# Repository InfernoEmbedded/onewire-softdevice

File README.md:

# About
This repository contains hardware designs and software for implementing slave devices using the [Maxim 1-Wire®](https://www.maximintegrated.com/en/products/digital/one-wire.html) protocol on the STM32 microcontrollers.

# Licensing
Hardware is licensed under the The [TAPR Open Hardware License Version 1.0](http://www.tapr.org/ohl.html)

Software, Firmware & Documentation is licensed under [GPLv3](https://www.gnu.org/licenses/gpl-3.0.en.html)

# Prerequisites
## Hardware Design
- [Kicad](http://kicad.org/)
- [ThisIsNotRocketScience Gerber Panelizer](https://github.com/ThisIsNotRocketScience/GerberTools)
- [OpenSCAD](http://www.openscad.org/)
- [Fusion 360](https://www.autodesk.com/products/fusion-360/overview)

## Firmware
- [Eclipse](http://www.eclipse.org/) on Windows (may work on Linux, untested)
- [System Workbench for STM32](http://www.openstm32.org/System+Workbench+for+STM32)
- [MBed](https://github.com/ARMmbed/mbed-os)

# Layout
The libs directory contains source code for the OneWireSlave library.

The devices directory contains schematics, PCBs & firmware for the client devices.

# Devices
## Template
A template schematic with the basics wired up.

## Splitter
A passive Y splitter that allows short CAT5 runs to be broken off the main bus. A typical use would be to allow a short run to be dropped down a wall to a sensor or switch panel. Optionally includes a DS18B20 for temperature sensing.

## DS2408 Emulator
A partial implementation of the DS2408 in software, used for initial testing of the 1-Wire® protocol, but is otherwise unmaintained and unsupported.

## DS2408 4 Channel Switch
A device that accepts 4 switches, and provides 4 solid state relays. A jumper allows the relays to operate independently, or forced to operate in on/off pairs (for roller shutter/projector screen control). Somewhat obsoleted by SoManySwitches.

## Fimware Updater
A sub-16KB bootloader which allows devices that implement the Inferno Embedded commands to update firmware over the bus. The included STM32F030X8.ld linker file stores the bootloader at the start of the flash region. Firmware that is designed to be flashed with this uses a modified linker file that stores the firmware with a 16kB offset.

Inferno Embedded commands allow the device to be rebooted into the bootloader so that they can be updated. The device can also be forced to remain in bootloader mode by shorting SWDAT on the SWD header to GND with a jumper.

## SoManySwitches
A device with 8 RJ45 jacks, which each permit 6 toggle or momentary switches to be connected to the 1-Wire® network. The device will be alarmed when a switch is activated, and can then be polled to identify which switch was activated.

## SoManySwitches Clientboard
A daughterboard for SoManySwitches, designed to be installed at the switch point. The RJ45 socket is broken out into pairs of Gnd/Switch, and pullup/pulldowns are provided to suppress spurious switch activations.

## Aircon Zone Controller
A device that controls up to 8 24VAC air conditioning dampers, following the PolyAire pinout:

| RJ45 Pin  | Signal |
| :-------: | :----- |
| 1         | N/C    |
| 2         | Open   |
| 3         | Open   |
| 4         | Neutral|
| 5         | Neutral|
| 6         | Close  |
| 7         | Close  |
| 8         | N/C    |

By setting the transition time for each damper, the controller can partially open them, allowing balancing to be achieved via software control.

## 4 Channel RGBW LED Controller
A device to control up to 4 channels of common-anode RGBW LED strips, at up to 48V. Fading from the current colour to a new one is handled locally. An external relay can be driven via the Inline SSR board, allowing the LED power supply to be shut down when no strips require power.

## Inline SSR
A small board with a solid state relay installed, designed to be mounted inline in a power cord. It connects to other boards via a headphone cable.

# Hardware Design
## Microcontroller
This software has been developed and tested on the [STM32F030R8 microcontroller](http://www.st.com/en/microcontrollers/stm32f030r8.html), an ARM Cortex-M0 with 64kB of flash & 8kB of RAM. We are running it at 48MHz using the internal RC oscillator. It may be possible to reduce the clock speed, but this is untested. They can be purchased for around AUD$1 each on [Aliexpress](https://www.aliexpress.com/item/20Pcs-STM32F030R8T6-STM32F030-LQFP64-ARM-new/32793433764.html).

Prototype testing can be performed on a [Nucleo-F030R8](https://developer.mbed.org/platforms/ST-Nucleo-F030R8/).

## Microcontroller Pin Usage
A single GPIO from the microcontroller is used to communicate over the 1-Wire® protocol. This is typically pin F0.

## RJ45 Pinout
| RJ45 Pin  | Signal |
| :-------: | :----- |
| 1         | Gnd    |
| 2         | +5V    |
| 3         | Gnd    |
| 4         | 1W Data|
| 5         | Gnd    |
| 6         | N/C    |
| 7         | +24V   |
| 8         | Gnd    |

# Software Design
# Runtime
The library sits on top of the Mbed runtime, altough it is more reliant on the lower level HAL APIs than the Mbed constructs. The bootloader uses a cut-down version of the runtime to allow it to fit within 16kB, however, the cost is that it cannot print to the serial port.

## Low Level (OneWireSlave.cpp)
This file contains the base class for implementing 1-Wire® protocol devices. It provides methods to send and receive data on the bus, and handles device enumeration. It consumes Timer6 which it uses to maintain a 1 uS timer for signal timing. It uses the low level HAL APIs for catching state changes on the GPIO line, as the InterruptIn class added too much latency.

## Protocol Level (SoftDevice.cpp)
This file defines how InfernoEmbedded devices communicate over 1wire. Each device reports a 64 bit type and 64 bit version, so only a single 1-Wire® family code is used (FE).

1wire commands are issued as follows:
Master:
Command Code (1 byte), Command data (up to 8 bytes), CRC8

Slave:
Command good/bad (1 byte)

Slave:
device response (chunks of up to 8 bytes)

Or...

Master:
Streaming data

A 64 bit status register is provided, and the device will show up in alarm scans if any bits are set. On powerup, bit 0 is set (Power-on), allowing the devices to be reinitialised if they need state from the master. The status register is cleared automatically after each read.

## Device Level (SwitchMaster.cpp & friends)
These files provide the device specific implementations. They define the 1-Wire® commands that are accepted, and interact with the user code via Listener classes. to allow designs to scale, the driver will report the number of implementations it supports (eg. switches), so that many physical variants can share the same code.

# Getting Started
## Development Environment
- Install Eclipse for C/C++ development
- Install [System Workbench for STM32 Eclipse plugins](http://www.openstm32.org/Installing+System+Workbench+for+STM32+from+Eclipse?structure=Documentation)
- Clone the mbed sources
`git clone https://github.com/ARMmbed/mbed-os.git`
- ~~Build the arm-nano-eabi toolchain by running build.sh in the toolchain directory~~
- Fetch the ARM official toolchain by running build-arm.sh in the toolchain directory
- use the scripts build.(bat|sh) and build-trace.(bat|sh) in the mbed directory to build the thin or trace-enabled builds of Mbed
- Import the mbed Eclipse project
- Import the Eclipse projects from this repository

## Hardware Tools
These will be useful during development
- [SWD Programmer](https://www.aliexpress.com/item/FREE-SHIPPING-ST-Link-V2-stlink-mini-STM8STM32-STLINK-simulator-download-programming-With-Cover/32237636491.html)
- [Sigrok](https://sigrok.org/wiki/PulseView) compatible [logic analyser](https://www.aliexpress.com/item/Free-Shipping-10sets-100-New-Arrival-USB-Logic-Analyze-24M-8CH-MCU-ARM-FPGA-DSP-debug/32234091842.html)
- [Nucleo-F030R8](http://au.element14.com/stmicroelectronics/nucleo-f030r8/nucleo-board-mcu/dp/2394225)

## Adding a new device
First, consider whether one of the existing device level drivers will do what you need, or can be expanded to achieve your goals (without straying too far from the intent of the driver). If you need to expand it, increment the version so that the client software (eg. OWFS) can identify what commands are available.

Next, create a frontend project that interacts with the device level driver. You may initially want to use a listener that uses the TRACE() macro rather than interacting with the hardware until you are happy with the protocol.

Finally, submit patches to OWFS that implement the new device driver. You can look at owfs/owlib/src/c/ow_ie_*.c to see how the existing drivers work. Important to note are the visibility functions, which allow a single family code to appear as many different devices.

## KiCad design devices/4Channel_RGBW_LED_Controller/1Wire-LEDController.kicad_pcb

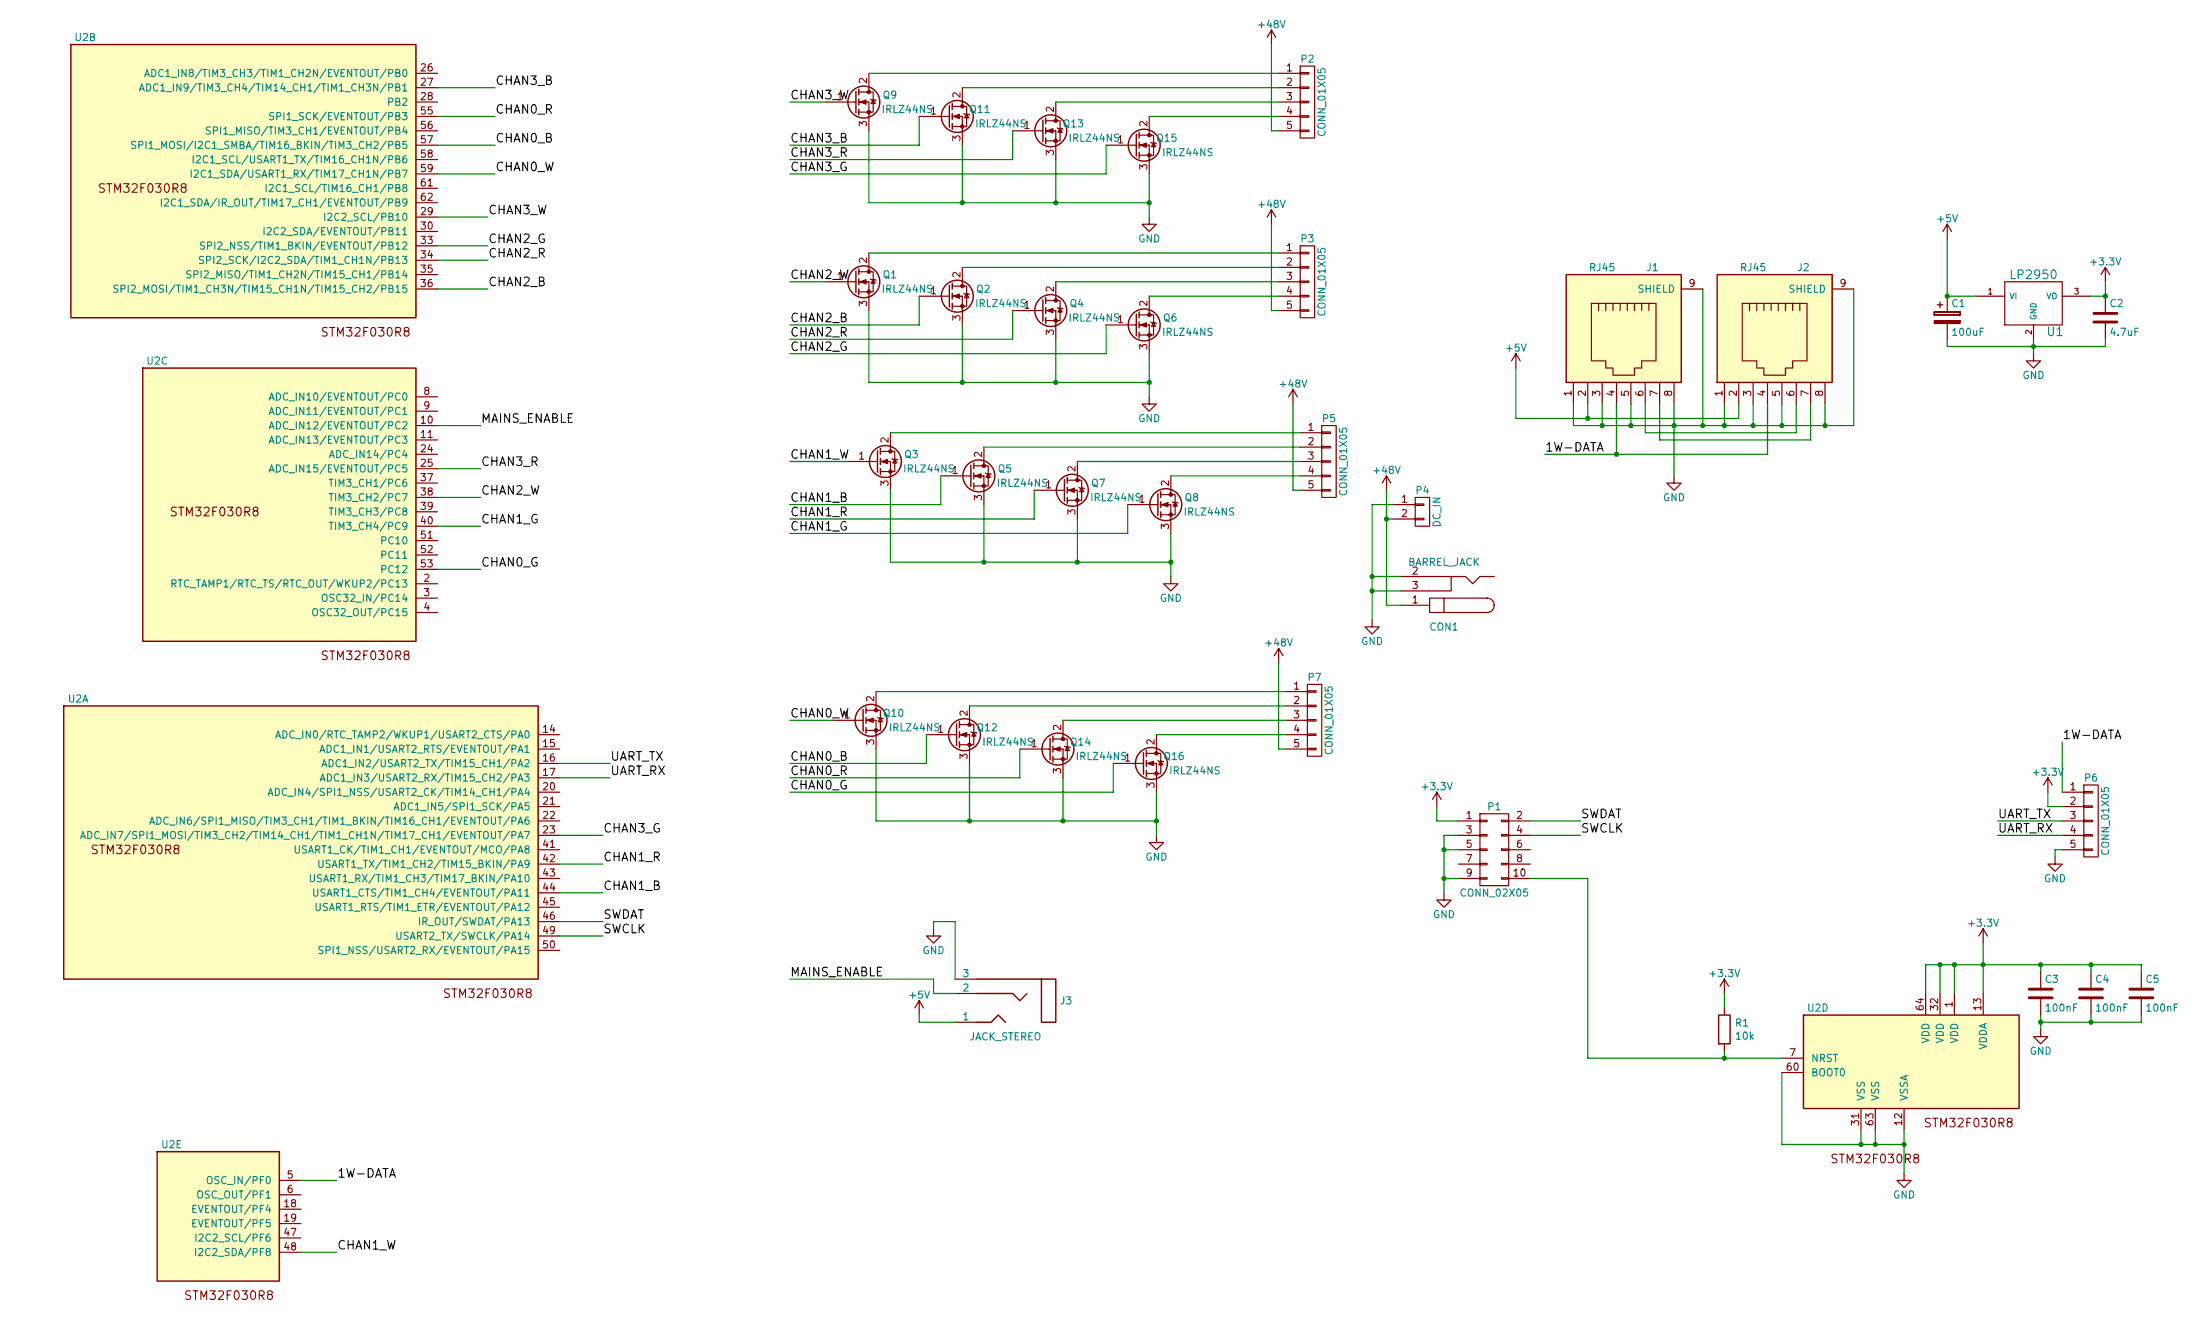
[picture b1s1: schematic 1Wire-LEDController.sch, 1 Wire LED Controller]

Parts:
C1: 100uF; c_elec_8x6.7
C2: 4.7uF; C_0603
C3, C4, C5: 100nF; C_0603
CON1: BARREL_JACK
J1, J2: RJ45; RJ45-ChinaSMD
J3: JACK_STEREO; jack_3.5_pj313d-smt
P1: CONN_02X05; Pin_Header_Straight_SMT_02x05
P2, P3, P5, P7: CONN_01X05; 2EDCK-5.08-5PIN
P4: DC_IN; 2EDCK-5.08-2PIN
P6: CONN_01X05; Pin_Header_Straight_1x05_Pitch2.54mm
Q1, Q2, Q3, Q4, Q5, Q6, Q7, Q8, Q9, Q10, Q11, Q12, Q13, Q14, Q15, Q16: IRLZ44NS; D2PAK
R1: 10k; R_0603
U1: LP2950; TO-252-2Lead
U2: STM32F030R8; LQFP-64_10x10mm_Pitch0.5mm

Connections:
+3V3: C2.1, C3.1, C4.1, C5.1, P1.1, P6.2, R1.1, U1.3 (VO), U2.1 (VDD), U2.13 (VDDA), U2.32 (VDD), U2.64 (VDD)
+5V: C1.1, J1.2, J2.2, J3.1, U1.1 (VI)
+48V: CON1.1, P2.5, P3.5, P4.2, P5.5, P7.5
/1W-DATA: J1.4, J2.4, P6.1, U2.5 (OSC_IN/PF0)
/CHAN0_B: Q12.1 (G), U2.57 (SPI1_MOSI/I2C1_SMBA/TIM16_BKIN/TIM3_CH2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)
/CHAN0_G: Q16.1 (G), U2.53 (PC12)
/CHAN0_R: Q14.1 (G), U2.55 (SPI1_SCK/EVENTOUT/PB3)
/CHAN0_W: Q10.1 (G), U2.59 (I2C1_SDA/USART1_RX/TIM17_CH1N/PB7)
/CHAN1_B: Q5.1 (G), U2.44 (USART1_CTS/TIM1_CH4/EVENTOUT/PA11)
/CHAN1_G: Q8.1 (G), U2.40 (TIM3_CH4/PC9)
/CHAN1_R: Q7.1 (G), U2.42 (USART1_TX/TIM1_CH2/TIM15_BKIN/PA9)
/CHAN1_W: Q3.1 (G), U2.48 (I2C2_SDA/PF8)
/CHAN2_B: Q2.1 (G), U2.36 (SPI2_MOSI/TIM1_CH3N/TIM15_CH1N/TIM15_CH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)
/CHAN2_G: Q6.1 (G), U2.33 (SPI2_NSS/TIM1_BKIN/EVENTOUT/PB12)
/CHAN2_R: Q4.1 (G), U2.34 (SPI2_SCK/I2C2_SDA/TIM1_CH1N/PB13)
/CHAN2_W: Q1.1 (G), U2.38 (TIM3_CH2/PC7)
/CHAN3_B: Q11.1 (G), U2.27 (ADC1_IN9/TIM3_CH4/TIM14_CH1/TIM1_CH3N/P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)
/CHAN3_G: Q15.1 (G), U2.23 (ADC_IN7/SPI1_MOSI/TIM3_CH2/TIM14_CH1/TI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)
/CHAN3_R: Q13.1 (G), U2.25 (ADC_IN15/EVENTOUT/PC5)
/CHAN3_W: Q9.1 (G), U2.29 (I2C2_SCL/PB10)
/MAINS_ENABLE: J3.2, U2.10 (ADC_IN12/EVENTOUT/PC2)
/SWCLK: P1.4, U2.49 (USART2_TX/SWCLK/PA14)
/SWDAT: P1.2, U2.46 (IR_OUT/SWDAT/PA13)
/UART_RX: P6.4, U2.17 (ADC1_IN3/USART2_RX/TIM15_CH2/PA3)
/UART_TX: P6.3, U2.16 (ADC1_IN2/USART2_TX/TIM15_CH1/PA2)
GND: C1.2, C2.2, C3.2, C4.2, C5.2, CON1.2, CON1.3, J1.1, J1.3, J1.5, J1.8, J1.9 (SHIELD), J2.1, J2.3, J2.5, J2.8, J2.9 (SHIELD), J3.3, P1.3, P1.5, P1.9, P4.1, P6.5, Q1.3 (S), Q2.3 (S), Q3.3 (S), Q4.3 (S), Q5.3 (S), Q6.3 (S), Q7.3 (S), Q8.3 (S), Q9.3 (S), Q10.3 (S), Q11.3 (S), Q12.3 (S), Q13.3 (S), Q14.3 (S), Q15.3 (S), Q16.3 (S), U1.2 (GND), U2.12 (VSSA), U2.31 (VSS), U2.60 (BOOT0), U2.63 (VSS)
unnamed: J1.6, J2.6
unnamed: J1.7, J2.7
unnamed: P1.10, R1.2, U2.7 (NRST)
unnamed: P2.1, Q9.2 (D)
unnamed: P2.2, Q11.2 (D)
unnamed: P2.3, Q13.2 (D)
unnamed: P2.4, Q15.2 (D)
unnamed: P3.1, Q1.2 (D)
unnamed: P3.2, Q2.2 (D)
unnamed: P3.3, Q4.2 (D)
unnamed: P3.4, Q6.2 (D)
unnamed: P5.1, Q3.2 (D)
unnamed: P5.2, Q5.2 (D)
unnamed: P5.3, Q7.2 (D)
unnamed: P5.4, Q8.2 (D)
unnamed: P7.1, Q10.2 (D)
unnamed: P7.2, Q12.2 (D)
unnamed: P7.3, Q14.2 (D)
unnamed: P7.4, Q16.2 (D)

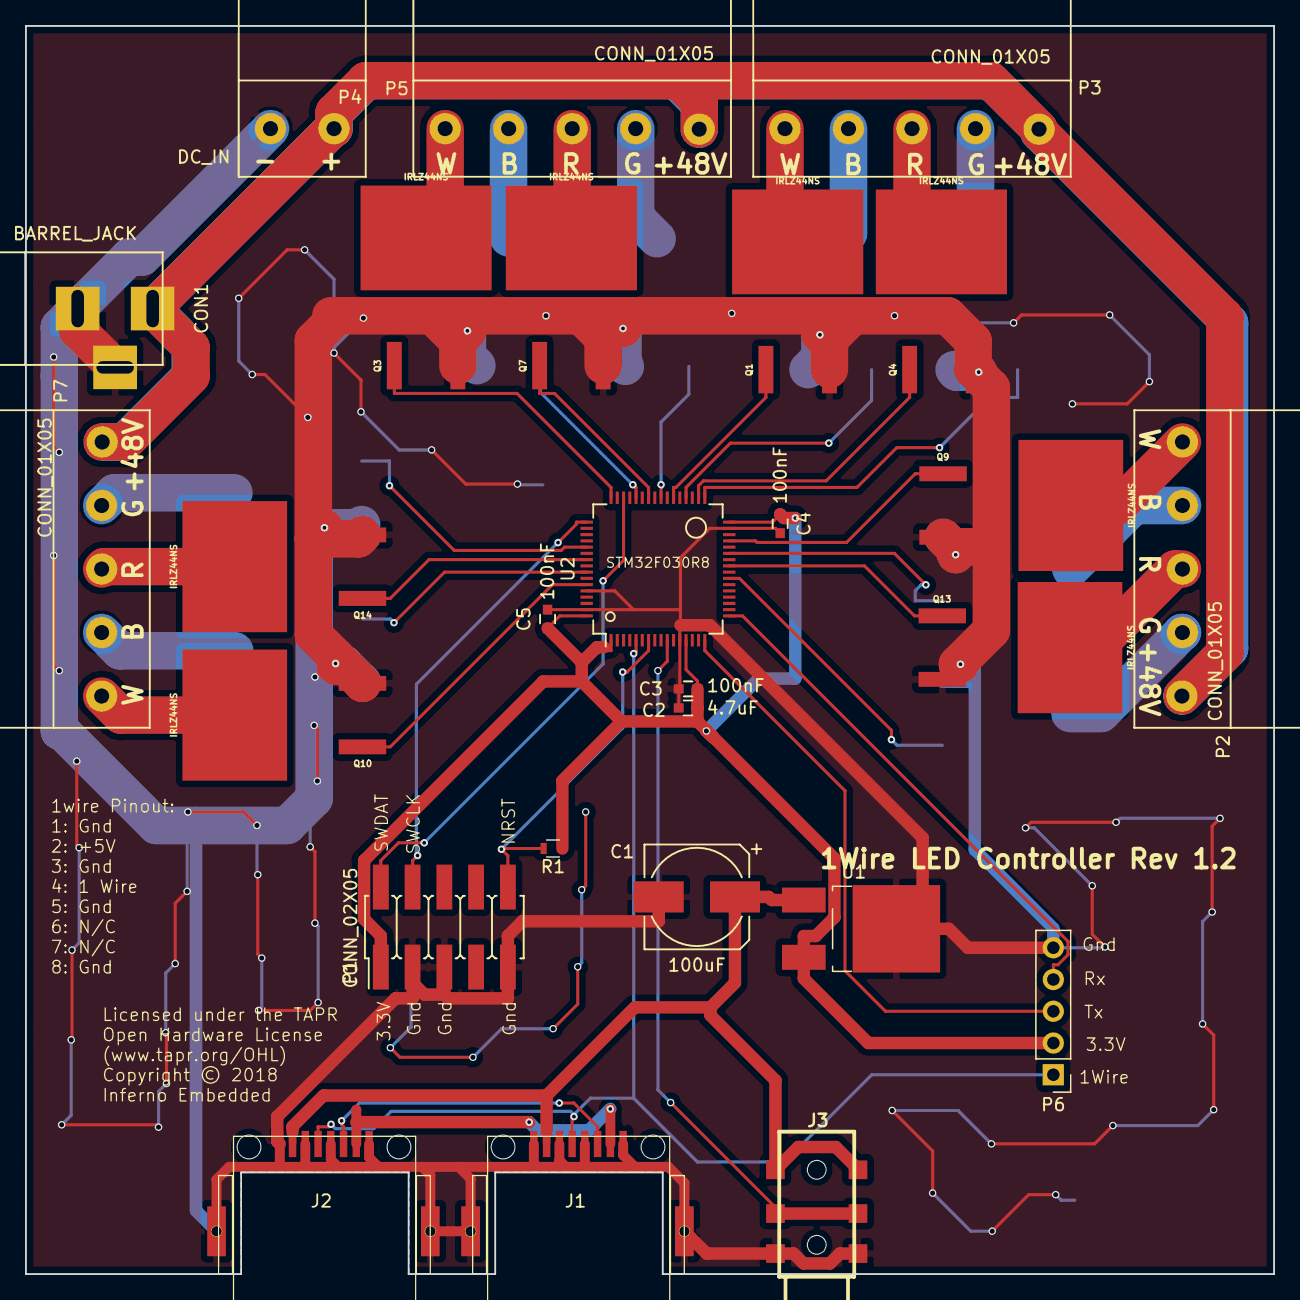
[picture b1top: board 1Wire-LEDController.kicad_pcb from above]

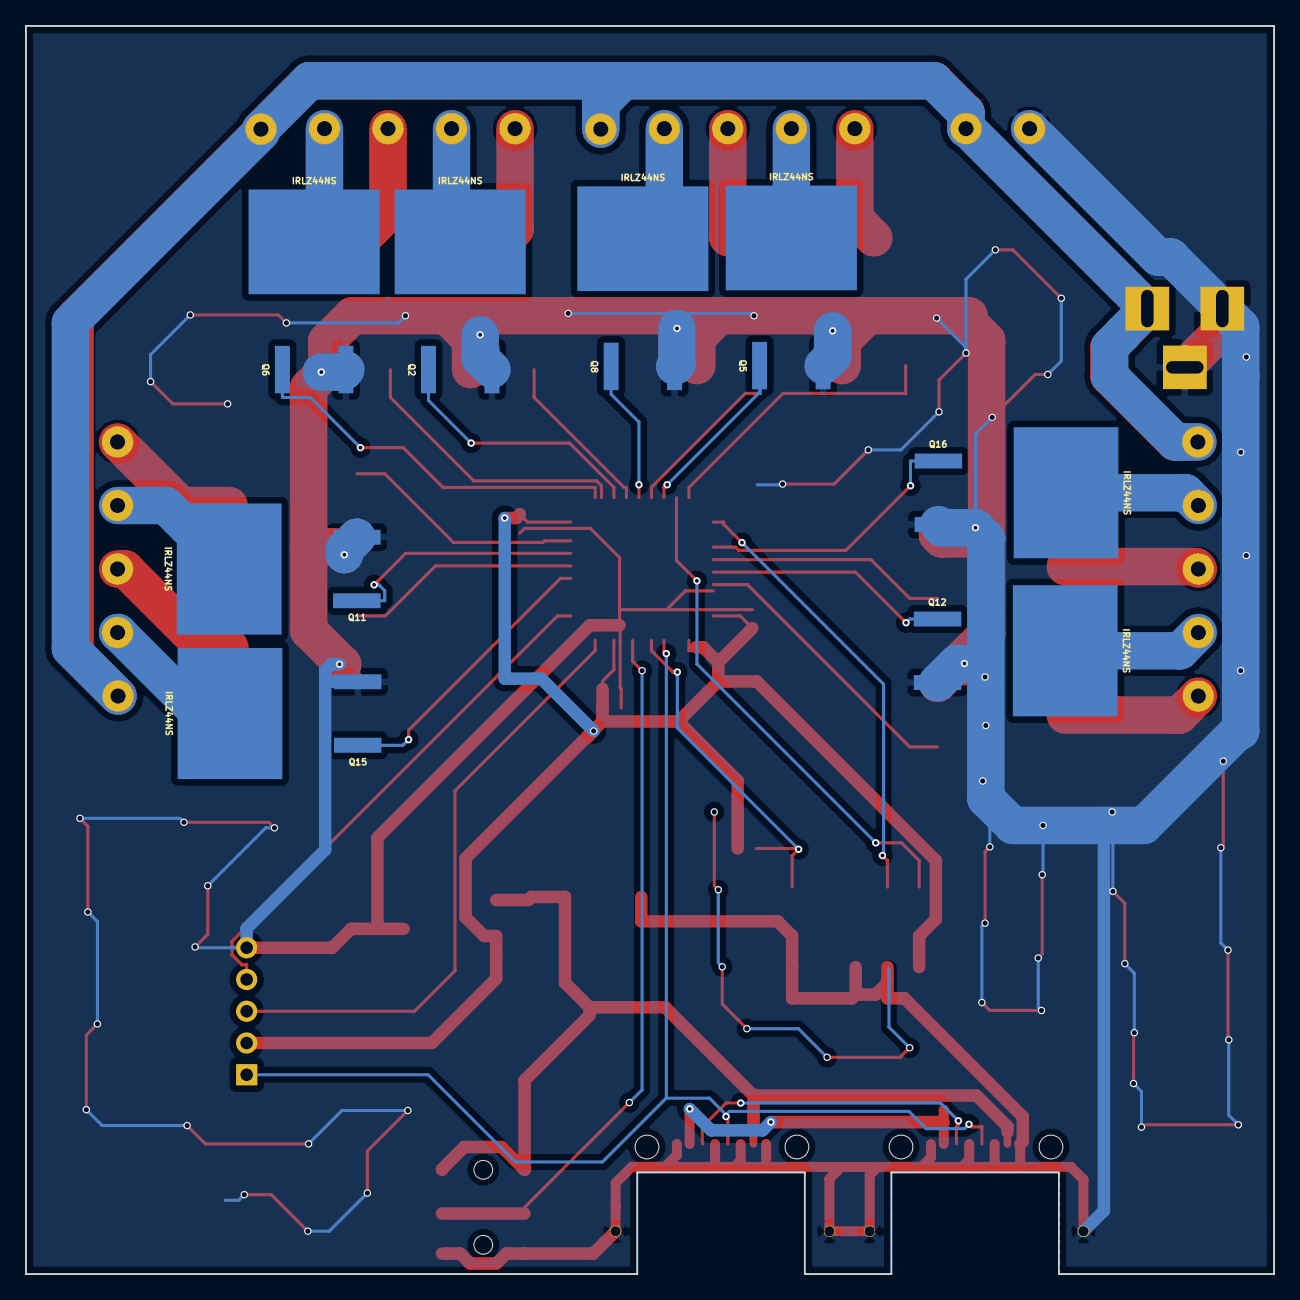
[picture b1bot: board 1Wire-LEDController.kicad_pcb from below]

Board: 2 copper layers, 99.8 x 99.8 mm, 35 parts (8 on the bottom side), 45 nets.

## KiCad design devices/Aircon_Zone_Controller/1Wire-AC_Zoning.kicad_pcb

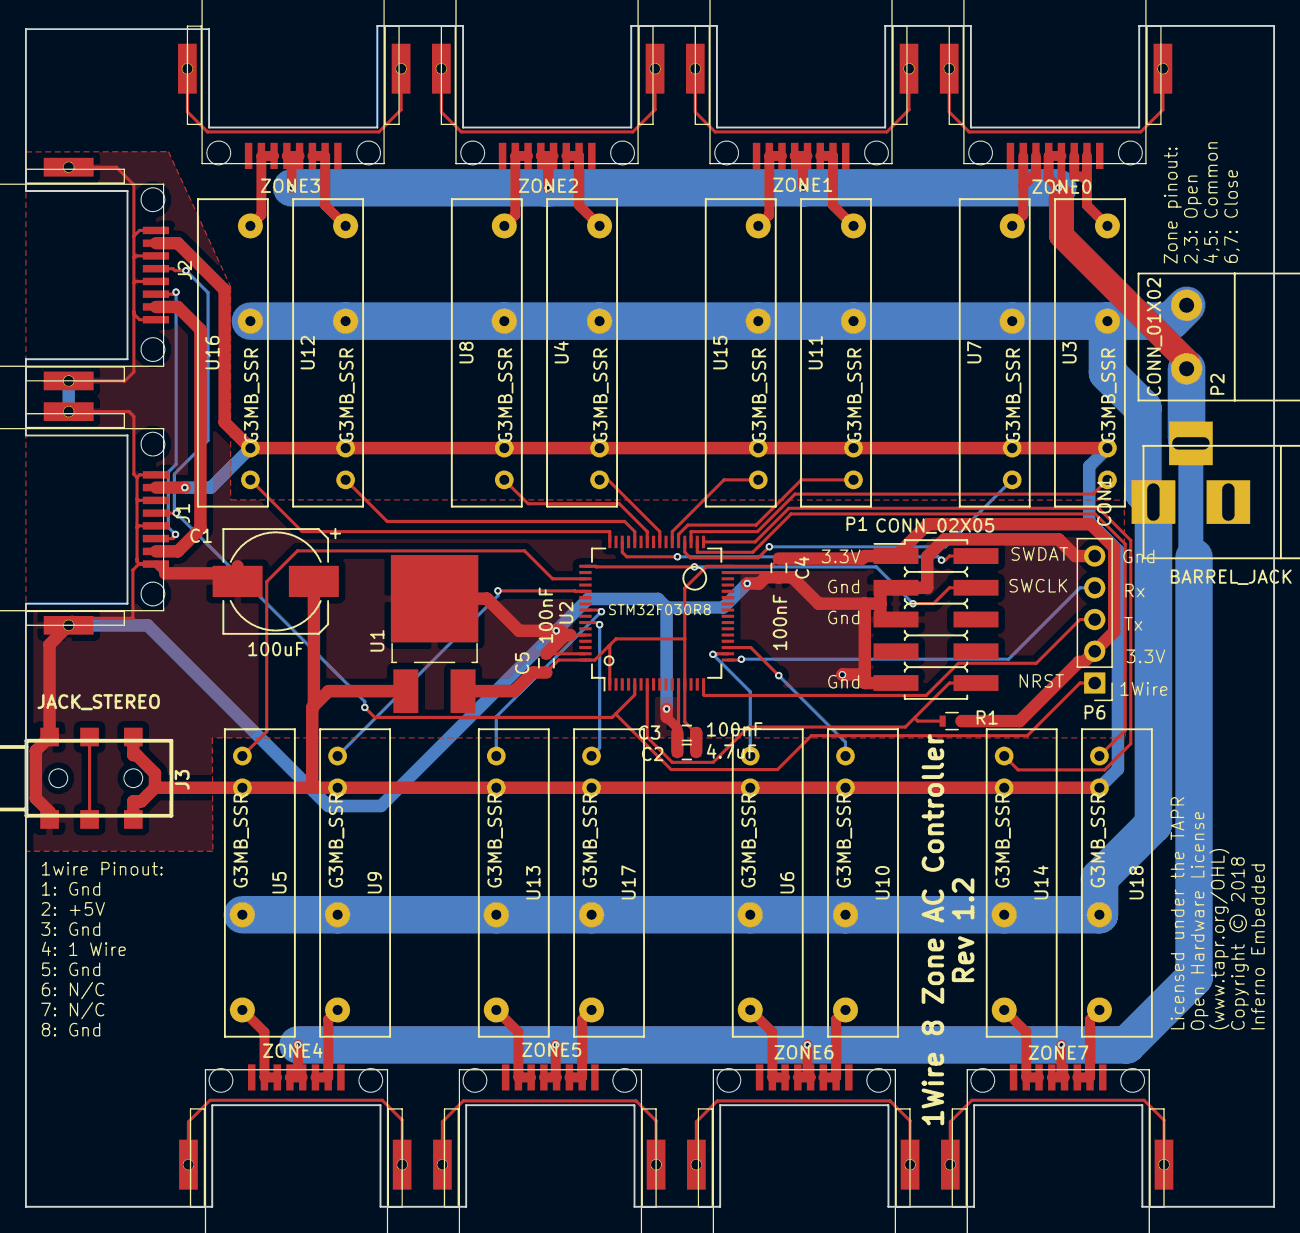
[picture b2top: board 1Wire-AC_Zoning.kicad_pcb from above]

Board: 2 copper layers, 99.9 x 94.5 mm, 39 parts (0 on the bottom side), 45 nets.

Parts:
C1: 100uF; c_elec_8x6.7
C2: 4.7uF; C_0603
C3, C4, C5: 100nF; C_0603
CON1: BARREL_JACK
J1, J2: RJ45; RJ45-ChinaSMD
J3: JACK_STEREO; jack_3.5_pj313d-smt
P1: CONN_02X05; Pin_Header_Straight_SMT_02x05
P2: CONN_01X02; 2EDCK-5.08-2PIN
P6: CONN_01X05; Pin_Header_Straight_1x05_Pitch2.54mm
R1: 33R; R_0603
U1: LP2950; TO-252-2Lead
U2: STM32F030R8; LQFP-64_10x10mm_Pitch0.5mm
U3, U4, U5, U6, U7, U8, U9, U10, U11, U12, U13, U14, U15, U16, U17, U18: G3MB_SSR; G3MB
ZONE0, ZONE1, ZONE2, ZONE3, ZONE4, ZONE5, ZONE6, ZONE7: RJ45; RJ45-ChinaSMD

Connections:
+3V3: C2.1, C3.1, C4.1, C5.1, P1.1, P6.2, R1.1, U1.3, U2.1, U2.13, U2.32, U2.64
+5V: C1.1, J1.2, J2.2, J3.1, U1.1, U3.3, U4.3, U5.3, U6.3, U7.3, U8.3, U9.3, U10.3, U11.3, U12.3, U13.3, U14.3, U15.3, U16.3, U17.3, U18.3
/1W-DATA: J1.4, J2.4, P6.1, U2.5
/24VAC_LIVE: CON1.1, P2.1, U3.2, U4.2, U5.2, U6.2, U7.2, U8.2, U9.2, U10.2, U11.2, U12.2, U13.2, U14.2, U15.2, U16.2, U17.2, U18.2
/24VAC_N: CON1.3, P2.2, ZONE0.4, ZONE0.5, ZONE1.4, ZONE1.5, ZONE2.4, ZONE2.5, ZONE3.4, ZONE3.5, ZONE4.4, ZONE4.5, ZONE5.4, ZONE5.5, ZONE6.4, ZONE6.5, ZONE7.4, ZONE7.5
/SWCLK: P1.4, U2.49
/SWDAT: P1.2, U2.46
/UART_RX: P6.4, U2.17
/UART_TX: P6.3, U2.16
/ZONE0_CLOSE: U2.36, U7.4
/ZONE0_OPEN: U2.35, U3.4
/ZONE1_CLOSE: U2.38, U15.4
/ZONE1_OPEN: U2.37, U11.4
/ZONE2_CLOSE: U2.42, U8.4
/ZONE2_OPEN: U2.40, U4.4
/ZONE3_CLOSE: U2.48, U16.4
/ZONE3_OPEN: U2.44, U12.4
/ZONE4_CLOSE: U2.53, U9.4
/ZONE4_OPEN: U2.51, U5.4
/ZONE5_CLOSE: U2.58, U17.4
/ZONE5_OPEN: U2.56, U13.4
/ZONE6_CLOSE: U2.19, U10.4
/ZONE6_OPEN: U2.18, U6.4
/ZONE7_CLOSE: U2.34, U18.4
/ZONE7_OPEN: U2.33, U14.4
GND: C1.2, C2.2, C3.2, C4.2, C5.2, J1.1, J1.3, J1.5, J1.8, J1.9, J2.1, J2.3, J2.5, J2.8, J2.9, J3.3, P1.3, P1.5, P1.9, P6.5, U1.2, U2.12, U2.31, U2.60, U2.63
unnamed: J1.6, J2.6
unnamed: J1.7, J2.7
unnamed: P1.10, R1.2, U2.7
unnamed: U3.1, ZONE0.2, ZONE0.3
unnamed: U4.1, ZONE2.2, ZONE2.3
unnamed: U5.1, ZONE4.2, ZONE4.3
unnamed: U6.1, ZONE6.2, ZONE6.3
unnamed: U7.1, ZONE0.6, ZONE0.7
unnamed: U8.1, ZONE2.6, ZONE2.7
unnamed: U9.1, ZONE4.6, ZONE4.7
unnamed: U10.1, ZONE6.6, ZONE6.7
unnamed: U11.1, ZONE1.2, ZONE1.3
unnamed: U12.1, ZONE3.2, ZONE3.3
unnamed: U13.1, ZONE5.2, ZONE5.3
unnamed: U14.1, ZONE7.2, ZONE7.3
unnamed: U15.1, ZONE1.6, ZONE1.7
unnamed: U16.1, ZONE3.6, ZONE3.7
unnamed: U17.1, ZONE5.6, ZONE5.7
unnamed: U18.1, ZONE7.6, ZONE7.7

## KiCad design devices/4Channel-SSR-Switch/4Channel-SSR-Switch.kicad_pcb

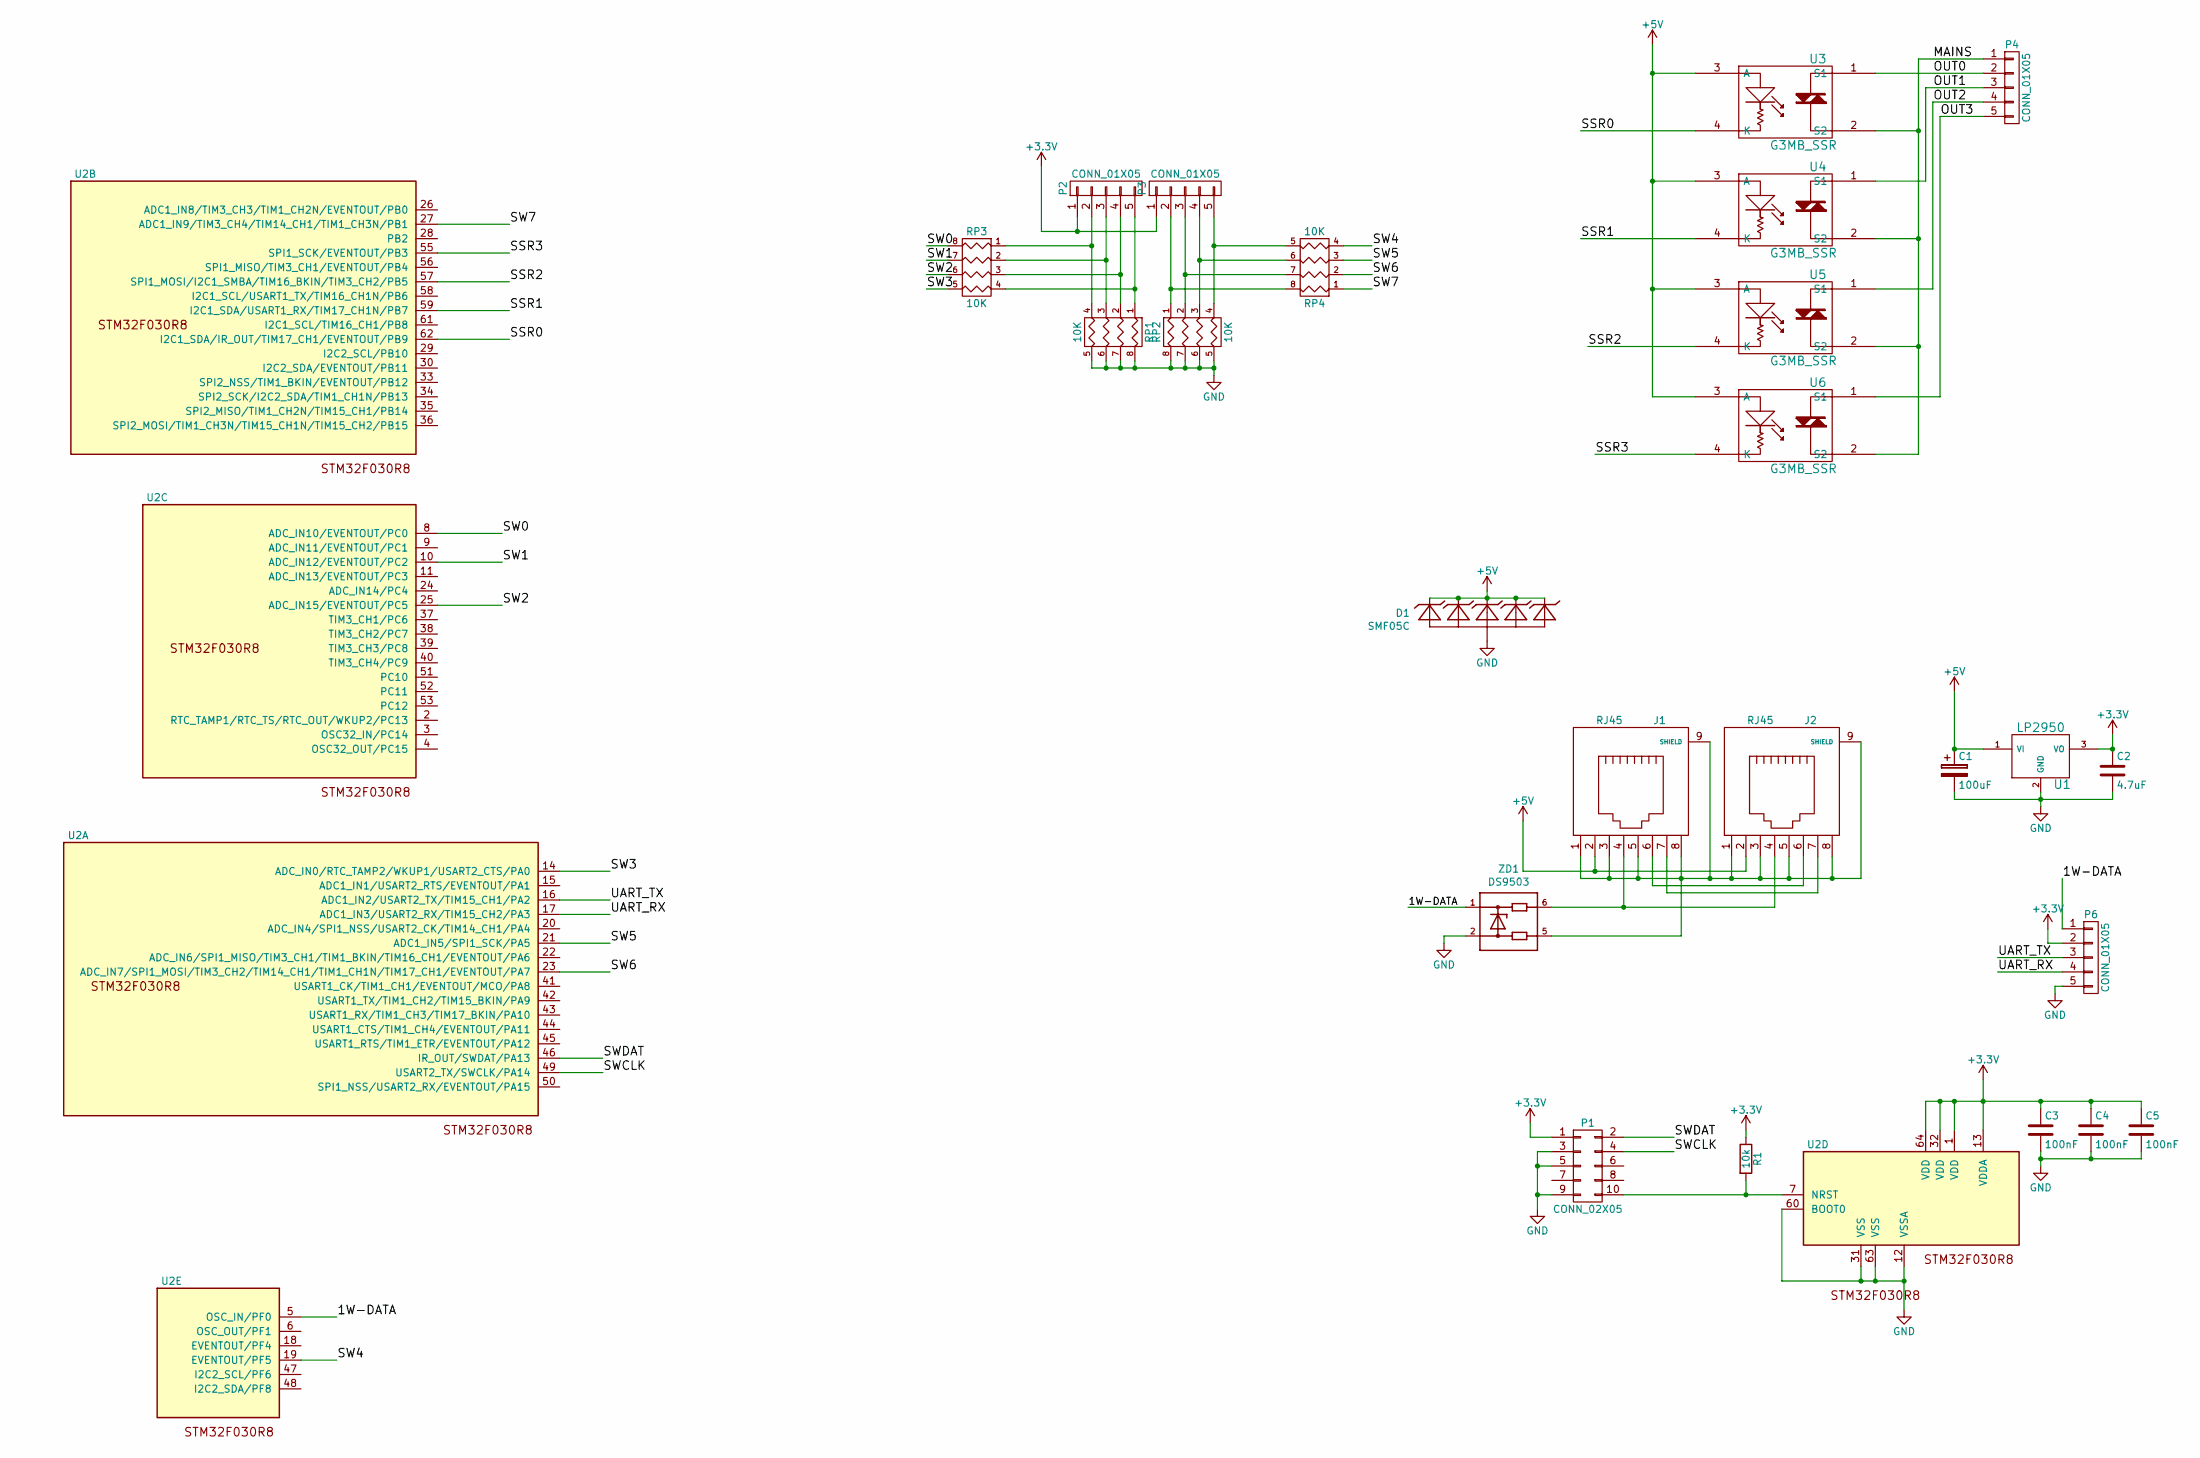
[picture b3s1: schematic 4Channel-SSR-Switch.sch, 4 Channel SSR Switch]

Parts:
C1: 100uF; C_1206
C2: 4.7uF; C_0603
C3, C4, C5: 100nF; C_0603
D1: SMF05C; SC70-6
J1, J2: RJ45; RJ45-ChinaSMD
P1: CONN_02X05; Pin_Header_Straight_2x05_Pitch2.54mm_SMD
P2, P3: CONN_01X05; Socket_MOLEX-KK-RM3-96mm_Lock_5pin_straight
P4: CONN_01X05; 2EDCK-5.08-5PIN
P6: CONN_01X05; Pin_Header_Straight_1x05_Pitch2.54mm
R1: 10k; R_0603
RP1, RP2, RP3, RP4: 10K; 0603_Pack4
U1: LP2950; TO-252-2
U2: STM32F030R8; LQFP-64_10x10mm_Pitch0.5mm
U3, U4, U5, U6: G3MB_SSR; G3MB
ZD1: DS9503; TSOC6

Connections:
+3V3: C2.1, C3.1, C4.1, C5.1, P1.1, P2.1, P3.1, P6.2, R1.1, U1.3 (VO), U2.1 (VDD), U2.13 (VDDA), U2.32 (VDD), U2.64 (VDD)
+5V: C1.1, D1.1 (C1), D1.3 (C2), D1.4 (C3), D1.5 (C4), D1.6 (C5), J1.2, J2.2, U1.1 (VI), U3.3 (A), U4.3 (A), U5.3 (A), U6.3 (A)
/1W-DATA: P6.1, U2.5 (OSC_IN/PF0), ZD1.1
/MAINS: P4.1, U3.2 (S2), U4.2 (S2), U5.2 (S2), U6.2 (S2)
/OUT0: P4.2, U3.1 (S1)
/OUT1: P4.3, U4.1 (S1)
/OUT2: P4.4, U5.1 (S1)
/OUT3: P4.5, U6.1 (S1)
/SSR0: U2.62 (I2C1_SDA/IR_OUT/TIM17_CH1/EVENTOUT/PB9), U3.4 (K)
/SSR1: U2.59 (I2C1_SDA/USART1_RX/TIM17_CH1N/PB7), U4.4 (K)
/SSR2: U2.57 (SPI1_MOSI/I2C1_SMBA/TIM16_BKIN/TIM3_CH2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), U5.4 (K)
/SSR3: U2.55 (SPI1_SCK/EVENTOUT/PB3), U6.4 (K)
/SW0: RP3.8 (R1), U2.8 (ADC_IN10/EVENTOUT/PC0)
/SW1: RP3.7 (R2), U2.10 (ADC_IN12/EVENTOUT/PC2)
/SW2: RP3.6 (R3), U2.25 (ADC_IN15/EVENTOUT/PC5)
/SW3: RP3.5 (R4), U2.14 (ADC_IN0/RTC_TAMP2/WKUP1/USART2_CTS/PA0)
/SW4: RP4.4, U2.19 (EVENTOUT/PF5)
/SW5: RP4.3, U2.21 (ADC1_IN5/SPI1_SCK/PA5)
/SW6: RP4.2, U2.23 (ADC_IN7/SPI1_MOSI/TIM3_CH2/TIM14_CH1/TI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)
/SW7: RP4.1, U2.27 (ADC1_IN9/TIM3_CH4/TIM14_CH1/TIM1_CH3N/P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)
/SWCLK: P1.4, U2.49 (USART2_TX/SWCLK/PA14)
/SWDAT: P1.2, U2.46 (IR_OUT/SWDAT/PA13)
/UART_RX: P6.4, U2.17 (ADC1_IN3/USART2_RX/TIM15_CH2/PA3)
/UART_TX: P6.3, U2.16 (ADC1_IN2/USART2_TX/TIM15_CH1/PA2)
GND: C1.2, C2.2, C3.2, C4.2, C5.2, D1.2 (A), P1.3, P1.5, P1.9, P6.5, RP1.5 (R4), RP1.6 (R3), RP1.7 (R2), RP1.8 (R1), RP2.5 (R4), RP2.6 (R3), RP2.7 (R2), RP2.8 (R1), U1.2 (GND), U2.12 (VSSA), U2.31 (VSS), U2.60 (BOOT0), U2.63 (VSS), ZD1.2
unnamed: J1.1, J1.3, J1.5, J1.8, J1.9 (SHIELD), J2.1, J2.3, J2.5, J2.8, J2.9 (SHIELD), ZD1.5
unnamed: J1.4, J2.4, ZD1.6
unnamed: J1.6, J2.6
unnamed: J1.7, J2.7
unnamed: P1.10, R1.2, U2.7 (NRST)
unnamed: P2.2, RP1.4, RP3.1
unnamed: P2.3, RP1.3, RP3.2
unnamed: P2.4, RP1.2, RP3.3
unnamed: P2.5, RP1.1, RP3.4
unnamed: P3.2, RP2.1, RP4.8 (R1)
unnamed: P3.3, RP2.2, RP4.7 (R2)
unnamed: P3.4, RP2.3, RP4.6 (R3)
unnamed: P3.5, RP2.4, RP4.5 (R4)

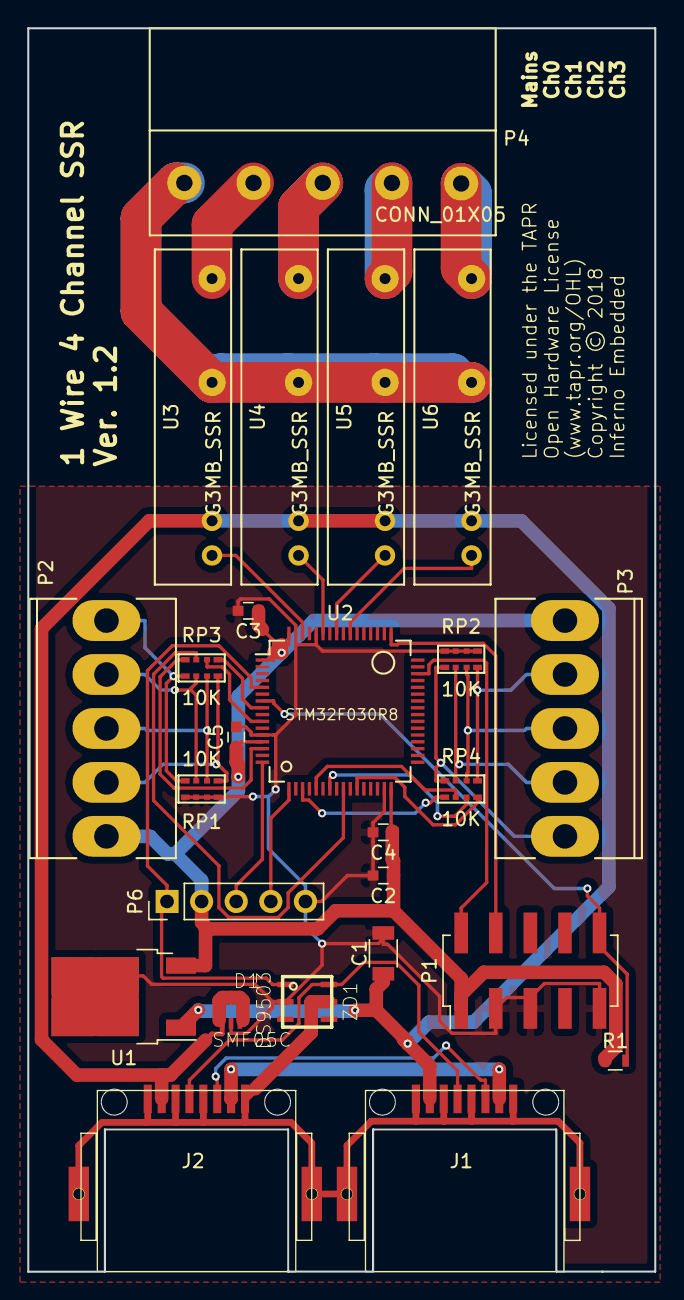
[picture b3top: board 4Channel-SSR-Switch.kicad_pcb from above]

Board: 2 copper layers, 46.0 x 91.3 mm, 25 parts (0 on the bottom side), 38 nets.

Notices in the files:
devices/16_Channel_SSR_Driver/16_Channel_SSR_Driver.kicad_pcb:
Copyright © 2018 Inferno Embedded
devices/DS2408-4channel-Switch/1wire-4switch.kicad_pcb:
©2016 Inferno Embedded
devices/Splitter/1wire-roof-module.kicad_pcb:
©2014 Inferno Embedded
